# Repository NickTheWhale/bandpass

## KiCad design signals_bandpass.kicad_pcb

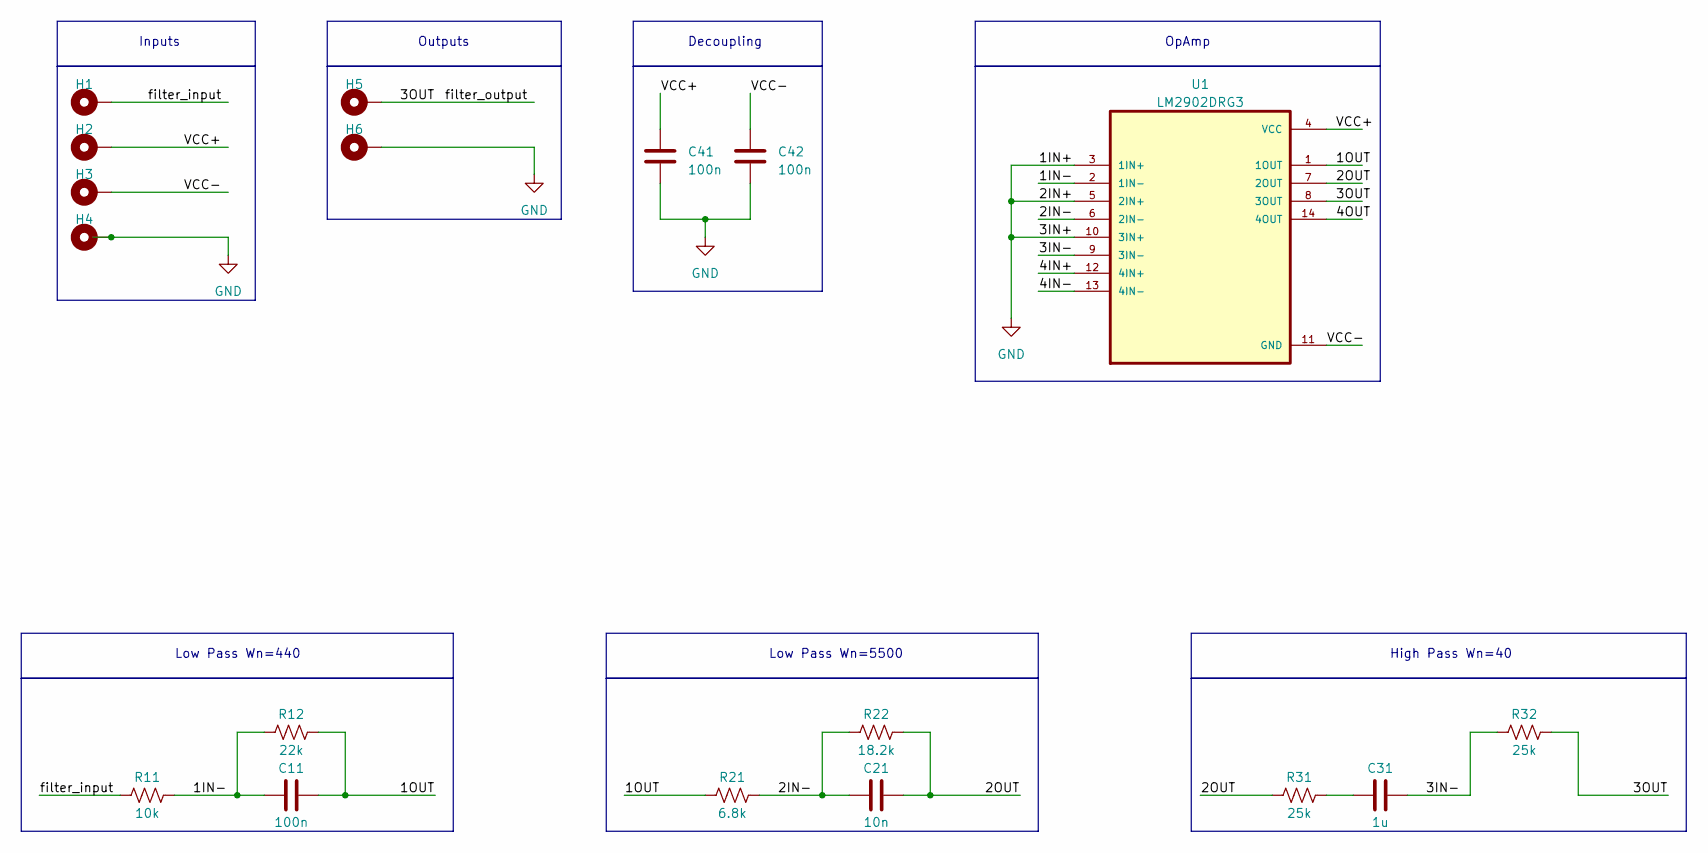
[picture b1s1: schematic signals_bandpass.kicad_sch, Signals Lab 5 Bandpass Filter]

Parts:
C11, C41, C42: 100n; C_0603_1608Metric
C21: 10n; C_0603_1608Metric
C31: 1u; C_0603_1608Metric
H1, H2, H3, H4, H5, H6: MountingHole_Pad; MountingHole_3.5mm_Pad_Via
R11: 10k; C_0603_1608Metric
R12: 22k; C_0603_1608Metric
R21: 6.8k; C_0603_1608Metric
R22: 18.2k; C_0603_1608Metric
R31, R32: 25k; R_0603_1608Metric
U1: LM2902DRG3; SOIC127P600X175-14N

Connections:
/1IN-: C11.1, R11.2, R12.1, U1.2 (1IN-)
/1OUT: C11.2, R12.2, R21.1, U1.1 (1OUT)
/2IN-: C21.1, R21.2, R22.1, U1.6 (2IN-)
/2OUT: C21.2, R22.2, R31.1, U1.7 (2OUT)
/3IN-: C31.2, R32.1, U1.9 (3IN-)
/3OUT: H5.1, R32.2, U1.8 (3OUT)
/4IN+: U1.12 (4IN+)
/4IN-: U1.13 (4IN-)
/4OUT: U1.14 (4OUT)
/VCC+: C41.2, H2.1, U1.4 (VCC)
/VCC-: C42.1, H3.1, U1.11 (GND)
/filter_input: H1.1, R11.1
GND: C41.1, C42.2, H4.1, H6.1, U1.3 (1IN+), U1.5 (2IN+), U1.10 (3IN+)
unnamed: C31.1, R31.2

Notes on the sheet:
OpAmp
Outputs
Decoupling
High Pass Wn=40
Low Pass Wn=440
Low Pass Wn=5500
Inputs

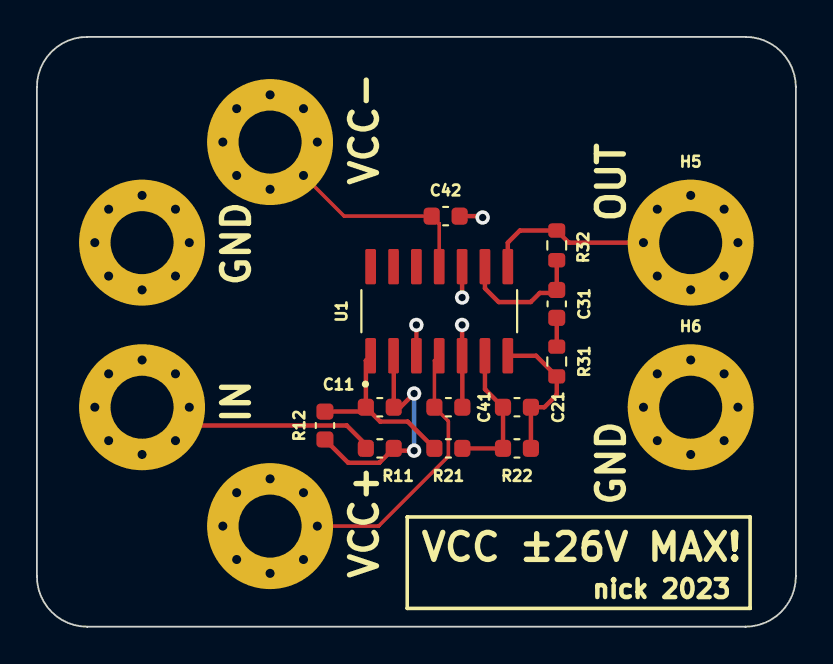
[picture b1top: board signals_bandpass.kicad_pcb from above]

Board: 2 copper layers, 42.2 x 32.8 mm, 18 parts (0 on the bottom side), 11 nets.

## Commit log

2023-05-11 init
2023-05-11 added screenshots
